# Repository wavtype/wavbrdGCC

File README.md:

# wavbrdGCC

ALL CREDIT FOR THE ORIGINAL PCB GOES TO PHOBOS AND HIS TEAM

aesthetically and functionally modified version of the PhobGCC

to contact me for whatever reason my discord is wav#9999

for more info on the PhobGCC project and it's development, visit these links below!

github - https://github.com/Phobos132/PhobGCC

discord - https://discord.gg/eNJ7xWMvxf

wiki - https://github.com/Phobos132/PhobGCC/wiki

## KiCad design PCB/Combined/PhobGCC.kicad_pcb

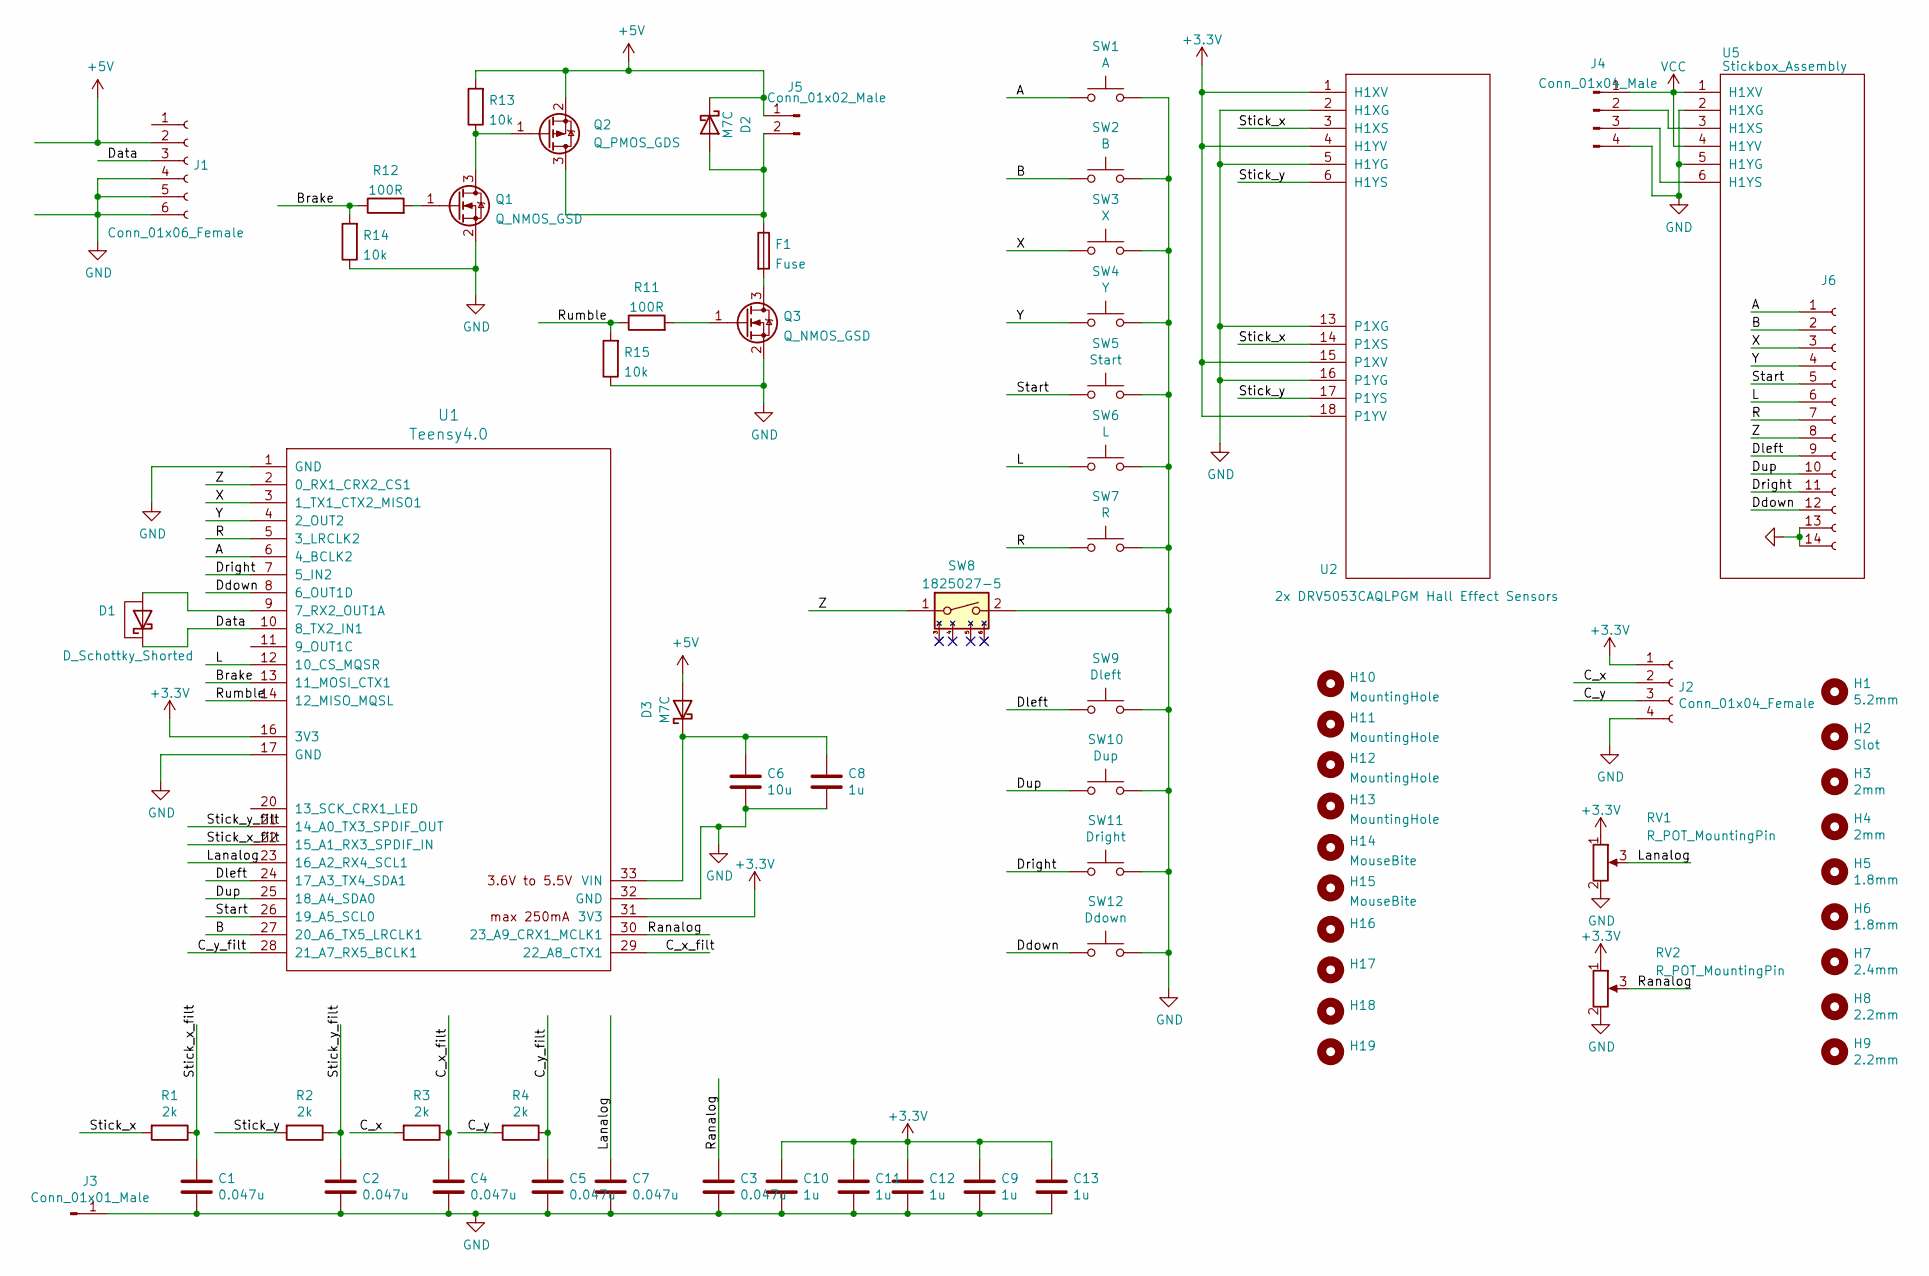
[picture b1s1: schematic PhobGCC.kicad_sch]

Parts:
C1, C2, C3, C4, C5, C7: 0.047u; LCSC C1622
C6: 10u; LCSC C19702
C8, C9, C10, C11, C12, C13: 1u; LCSC C15849
D1: D_Schottky_Shorted
D2, D3: M7C; LCSC C8598
F1: Fuse; LCSC C69680
H1: 5.2mm
H2: Slot
H3, H4: 2mm
H5, H6: 1.8mm
H7: 2.4mm
H8, H9: 2.2mm
H10, H11, H12, H13: MountingHole
H14, H15: MouseBite
H16, H17, H18, H19: (no value)
J1: Conn_01x06_Female
J2: Conn_01x04_Female
J3: Conn_01x01_Male
J4: Conn_01x04_Male
J5: Conn_01x02_Male
J6: (no value)
Q1, Q3: Q_NMOS_GSD; LCSC C20917
Q2: Q_PMOS_GDS; LCSC C15127
R1: 2k; Manufacturer PN 0603WAF1002T5ECopy; LCSC C22975
R2, R3, R4: 2k; LCSC C22975
R11, R12: 100R; LCSC C22775
R13, R14, R15: 10k; LCSC C25804
RV1, RV2: R_POT_MountingPin
SW1: A
SW2: B
SW3: X
SW4: Y
SW5: Start
SW6: L
SW7: R
SW8: 1825027-5
SW9: Dleft
SW10: Dup
SW11: Dright
SW12: Ddown
U1: Teensy4.0
U2: 2x DRV5053CAQLPGM Hall Effect Sensors
U5: Stickbox_Assembly

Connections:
+3V3: C9.1, C10.1, C11.1, C12.1, C13.1, J2.1, RV1.1 (V+), RV2.1 (V+), U1.16 (3V3), U1.31 (3V3), U2.1 (H1XV), U2.4 (H1YV), U2.15 (P1XV), U2.18 (P1YV)
+5V: D2.1 (K), D3.2 (A), J1.2, J5.1, Q2.2 (S), R13.2
/A: J6.1, SW1.1, U1.6 (4_BCLK2)
/B: J6.2, SW2.1, U1.27 (20_A6_TX5_LRCLK1)
/Brake: R12.1, R14.2, U1.13 (11_MOSI_CTX1)
/C_x: J2.2, R3.2
/C_x_filt: C4.1, R3.1, U1.29 (22_A8_CTX1)
/C_y: J2.3, R4.2
/C_y_filt: C5.1, R4.1, U1.28 (21_A7_RX5_BCLK1)
/Data: D1.1 (K), J1.3, U1.10 (8_TX2_IN1)
/Ddown: J6.12, SW12.1, U1.8 (6_OUT1D)
/Dleft: J6.9, SW9.1, U1.24 (17_A3_TX4_SDA1)
/Dright: J6.11, SW11.1, U1.7 (5_IN2)
/Dup: J6.10, SW10.1, U1.25 (18_A4_SDA0)
/L: J6.6, SW6.1, U1.12 (10_CS_MQSR)
/Lanalog: C7.1, RV1.3 (Signal), U1.23 (16_A2_RX4_SCL1)
/R: J6.7, SW7.1, U1.5 (3_LRCLK2)
/Ranalog: C3.1, RV2.3 (Signal), U1.30 (23_A9_CRX1_MCLK1)
/Rumble: R11.1, R15.2, U1.14 (12_MISO_MQSL)
/Start: J6.5, SW5.1, U1.26 (19_A5_SCL0)
/Stick_x: R1.2, U2.3 (H1XS), U2.14 (P1XS)
/Stick_x_filt: C1.1, R1.1, U1.22 (15_A1_RX3_SPDIF_IN)
/Stick_y: R2.2, U2.6 (H1YS), U2.17 (P1YS)
/Stick_y_filt: C2.1, R2.1, U1.21 (14_A0_TX3_SPDIF_OUT)
/X: J6.3, SW3.1, U1.3 (1_TX1_CTX2_MISO1)
/Y: J6.4, SW4.1, U1.4 (2_OUT2)
/Z: J6.8, SW8.1, U1.2 (0_RX1_CRX2_CS1)
unnamed: C6.1, C8.1, D3.1 (K), U1.33 (VIN)
unnamed: D1.2 (A), U1.9 (7_RX2_OUT1A)
unnamed: D2.2 (A), F1.1, J5.2, Q2.3 (D)
unnamed: F1.2, Q3.3 (D)
unnamed: J4.2, U5.3 (H1XS)
unnamed: J4.3, U5.6 (H1YS)
unnamed: Q1.1 (G), R12.2
unnamed: Q1.3 (D), Q2.1 (G), R13.1
unnamed: Q3.1 (G), R11.2
VCC: J4.1, U5.1 (H1XV), U5.4 (H1YV)

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
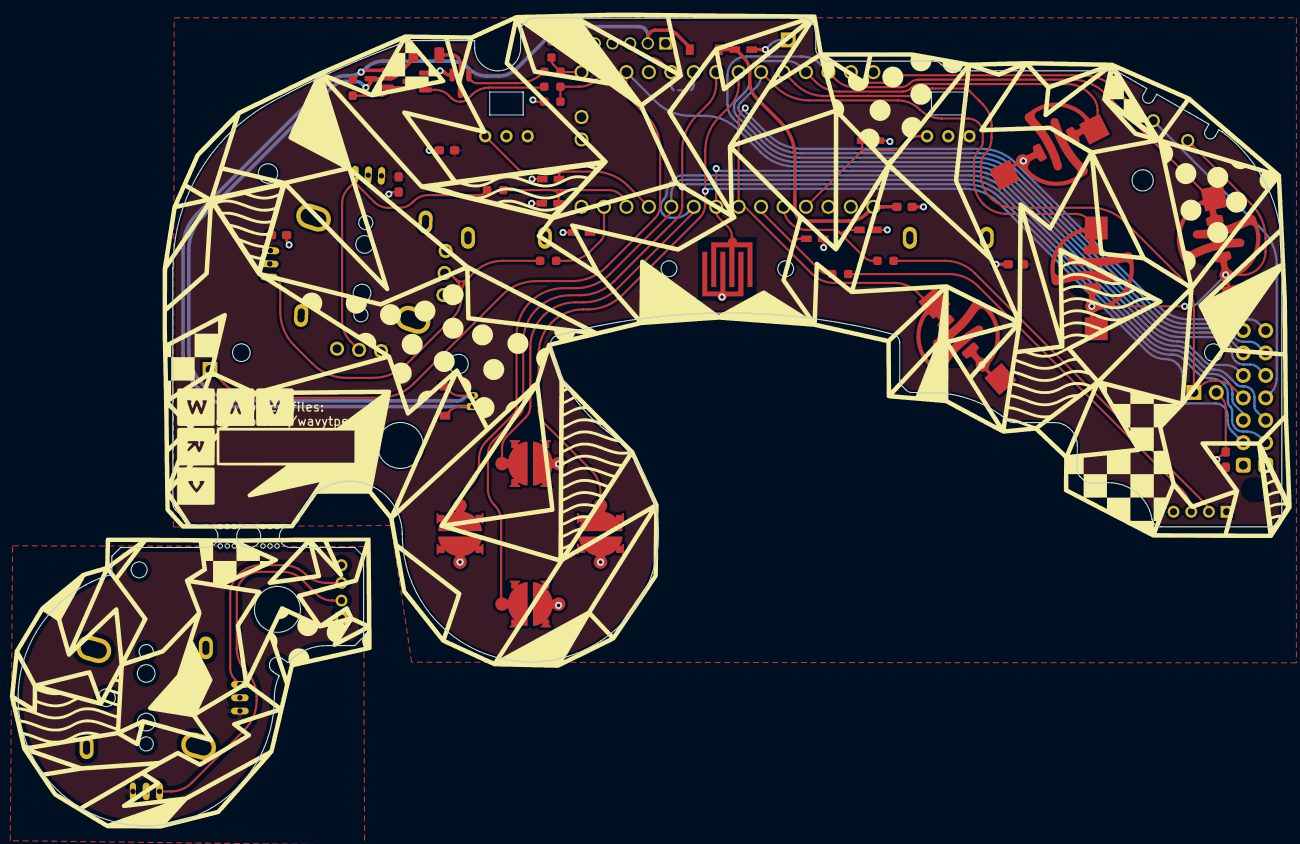
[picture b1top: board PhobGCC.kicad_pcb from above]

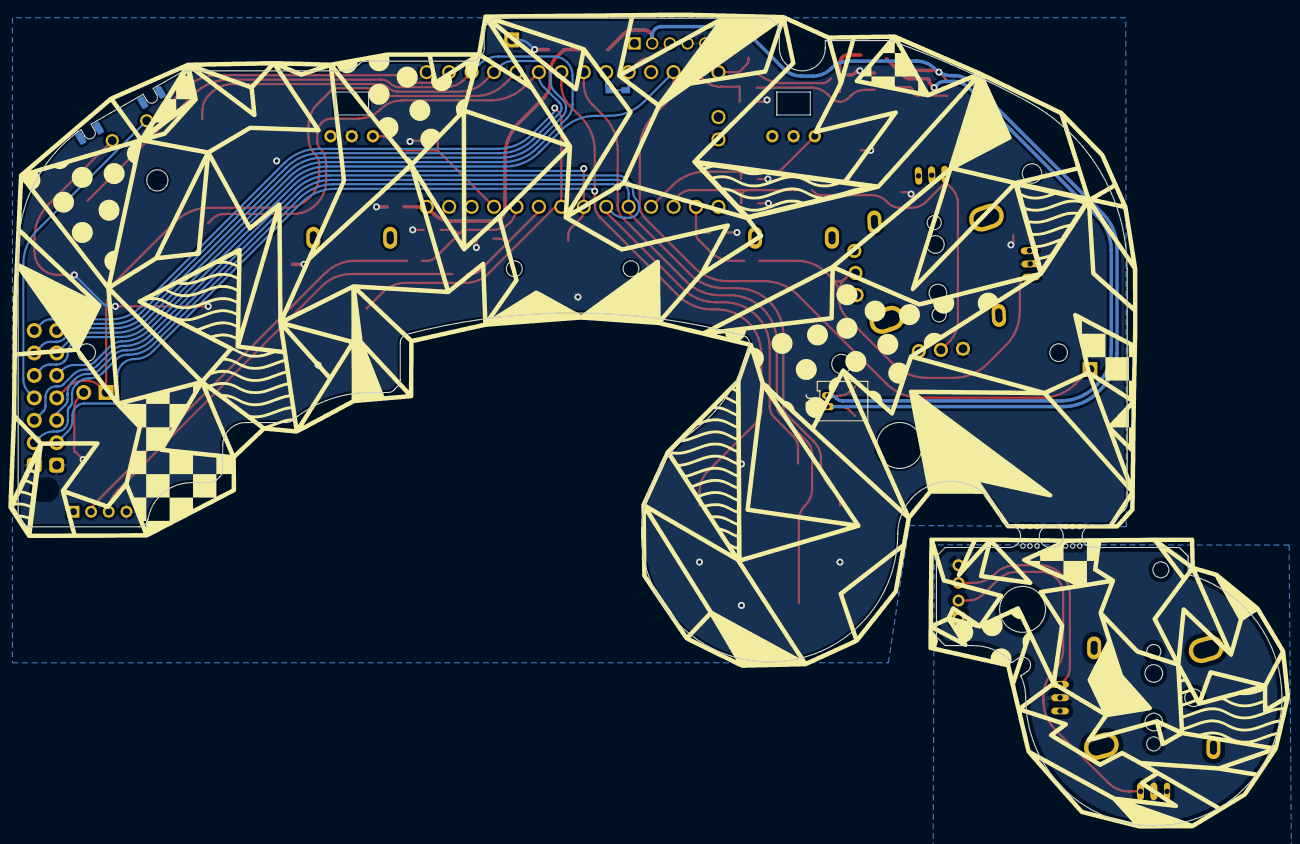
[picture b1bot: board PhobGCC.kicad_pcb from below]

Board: 2 copper layers, 143.0 x 91.4 mm, 71 parts (9 on the bottom side), 38 nets.

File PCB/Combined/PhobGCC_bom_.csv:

Component,Description,Part,References,Value,Footprint,Quantity Per PCB,Datasheet,LCSC,Manufacturer PN,Comment,Configuration_Pole-Throw,Contact_Current_Rating,EU_RoHS_Compliance,Note
1,Unpolarized capacitor,C,C1 C2 C3 C4 C5 C7,0.047u,C_0603_HandSoldering,6,~,C1622,,,,,,
2,Unpolarized capacitor,C,C8 C9 C10 C11 C12 C13,1u,C_0603_1608Metric_Pad1.08x0.95mm_HandSolder,6,~,C15849,,,,,,
3,Unpolarized capacitor,C,C6,10u,C_0603_HandSoldering,1,~,C19702,,,,,,
4,Schottky diode,D_Schottky_Shorted,D1,D_Schottky_Shorted,D_SOD-523_Shorted,1,~,,,,,,,
5,Schottky diode,D_Schottky,D2 D3,M7C,D_SOD-123,2,~,C8598,,,,,,
6,Fuse,Fuse,F1,Fuse,R_1206_3216Metric,1,~,C69680,,,,,,
7,"Generic connector, single row, 01x01, script generated (kicad-library-utils/schlib/autogen/connector/)",Conn_01x01_Male,J3,Conn_01x01_Male,PinHeader_1x01_P2.54mm_Vertical,1,~,,,,,,,
8,"Generic connector, single row, 01x02, script generated (kicad-library-utils/schlib/autogen/connector/)",Conn_01x02_Male,J5,Conn_01x02_Male,PinHeader_1x02_P2.54mm_Vertical,1,~,,,,,,,
9,"Generic connector, single row, 01x04, script generated (kicad-library-utils/schlib/autogen/connector/)",Conn_01x04_Female,J2,Conn_01x04_Female,Pin_Header_Straight_1x04_Pitch2.00mm,1,~,,,,,,,
10,"Generic connector, single row, 01x06, script generated (kicad-library-utils/schlib/autogen/connector/)",Conn_01x06_Female,J1,Conn_01x06_Female,GCC_Header_Straight_1x06_Pitch2.00mm,1,~,,,,,,,
11,"N-MOSFET transistor, gate/source/drain",Q_NMOS_GSD,Q1 Q3,Q_NMOS_GSD,SOT-23,2,~,C20917,,,,,,
12,"P-MOSFET transistor, gate/source/drain",Q_PMOS_GSD,Q2,Q_PMOS_GDS,SOT-23,1,~,C15127,,,,,,
13,Resistor,R,R11 R12,100R,R_0603_1608Metric_Pad0.98x0.95mm_HandSolder,2,~,C22775,,,,,,
14,Resistor,R,R1 R2 R3 R4,2k,R_0603_1608Metric_Pad0.98x0.95mm_HandSolder,4,~,C22975,0603WAF1002T5ECopy,,,,,
15,Resistor,R,R13 R14 R15,10k,R_0603_1608Metric_Pad0.98x0.95mm_HandSolder,3,~,C25804,,,,,,
16,,Gamecube-MB-rescue_Slider_GCC-Gamecube_MB,RV1 RV2,R_POT_MountingPin,GCC_Slider,2,,,,,,,,
17,"1x DIP Switch, Single Pole Single Throw (SPST) switch, small symbol",SW_DIP_x01,SW8,1825027-5,Z_Switch_Edge,1,~,,,1825027-5,Single Pole - Single Throw,50 mA,Compliant,
18,"Push button switch, generic, two pins",SW_Push,SW1,A,ABXY_Contact_Omron_Switch,1,~,,,,,,,
19,"Push button switch, generic, two pins",SW_Push,SW2,B,ABXY_Contact_Omron_Switch,1,~,,,,,,,
20,"Push button switch, generic, two pins",SW_Push,SW12,Ddown,Dpad_Contact_TL3315NF_2,1,~,,,,,,,
21,"Push button switch, generic, two pins",SW_Push,SW9,Dleft,Dpad_Contact_TL3315NF_2,1,~,,,,,,,
22,"Push button switch, generic, two pins",SW_Push,SW11,Dright,Dpad_Contact_TL3315NF_2,1,~,,,,,,,
23,"Push button switch, generic, two pins",SW_Push,SW10,Dup,Dpad_Contact_TL3315NF_2,1,~,,,,,,,
24,"Push button switch, generic, two pins",SW_Push,SW6,L,Pin_Header_Straight_1x02_Pitch2.54mm,1,~,,,,,,,
25,"Push button switch, generic, two pins",SW_Push,SW7,R,Pin_Header_Straight_1x02_Pitch2.54mm,1,~,,,,,,,
26,"Push button switch, generic, two pins",SW_Push,SW5,Start,Start_Contact,1,~,,,,,,,
27,"Push button switch, generic, two pins",SW_Push,SW3,X,ABXY_Contact_Omron_Switch,1,~,,,,,,,
28,"Push button switch, generic, two pins",SW_Push,SW4,Y,ABXY_Contact_Omron_Switch,1,~,,,,,,,
29,,Gamecube-MB-rescue_Stickbox_Assembly-Gamecube_MB,U2,2x DRV5053CAQLPGM Hall Effect Sensors,GCC_Stickbox_2,1,,,,,,,,
30,"Subminiature Reflective Optical Sensor, SMD-package with PCB-cutout",BPR-105,U3 U4,GP2S60-MFG,Sharp_Microelectronics-GP2S60-MFG,2,http://www.ystone.com.tw/en/data/goods/IRPT/Photo%20Interrup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,,,,,,,DNP
31,,Teensy4.0,U1,Teensy4.0,Teensy40_Edge_Pins,1,,,,,,,,





Component Groups:,32
Component Count:,57
Fitted Components:,51
Number of PCBs:,1
Total components:,51
Schematic Version:,
Schematic Date:,
PCB Variant:,default
BoM Date:,5/21/2022 5:21:06 PM
Schematic Source:,PhobGCC.kicad_sch
KiCad Version:,Eeschema (6.0.4)

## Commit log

2022-05-25 added PCB photo
2022-05-26 rebuild for 1.2.1
    added JST connector for rumble, button pinout, fixed outline, removed unused trigger sensors.
2022-05-26 new cover photo
2022-05-26 fixed silk in gerber
2022-05-26 hatched fill
2022-05-26 hatched fill added
2022-05-26 removed extra VIA
2022-05-30 flipped trigger boards
2022-06-01 new mousebites and buttons
2022-06-02 1.2.2 update
2022-08-04 1.2.3 update
2022-10-17 Update README.md
    wavbrd 1.2.X
2022-10-17 1.2.X overhaul
2022-10-17 marked old as old
2022-11-02 1.2.X final tweaks
